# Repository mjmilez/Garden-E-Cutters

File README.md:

# Garden E-Cutters

## Overview
The Garden E-Cutters shears are a smart harvesting tool that records each cut event along with high-accuracy GPS data. When a cut is detected, the system captures an RTK-corrected GNSS position, logs the event locally, and transmits it to a base station for visualization on a live map dashboard.

## Key Features
- RTK GNSS positioning (u-blox ZED-F9P) for centimeter-level accuracy  
- Hall effect sensor-based cut detection  
- ESP32-based embedded control system  
- Local CSV logging for offline reliability  
- Bluetooth Low Energy (BLE) data transfer to base station  
- Audible and LED feedback for user interaction  
- Debounced trigger logic to prevent duplicate cut events  

## How It Works
1. A cut is detected using a Hall effect sensor on the shears.  
2. The ESP32 captures the next valid GNSS (GNGGA) message from the ZED-F9P.  
3. The event (timestamp + GPS + fix data) is stored locally in a CSV buffer.  
4. When connected, data is transmitted over BLE to the base station.  
5. The base system visualizes cut locations on a map dashboard.

## Hardware
- ESP32 microcontroller  
- u-blox ZED-F9P RTK GNSS receiver  
- Hall effect sensor (cut detection)  
- Piezo buzzer (status feedback)  
- Status LEDs  
- Battery-powered field enclosure  

## Design Focus
- Low-latency cut-to-log workflow  
- Reliable operation under intermittent connectivity  
- Minimal power and compute load on the field device  
- Robust data capture even during GNSS or BLE interruptions  

## Status
Prototype validated in field-like testing with reliable event detection, RTK-level positioning, and stable end-to-end data transfer to the base system.

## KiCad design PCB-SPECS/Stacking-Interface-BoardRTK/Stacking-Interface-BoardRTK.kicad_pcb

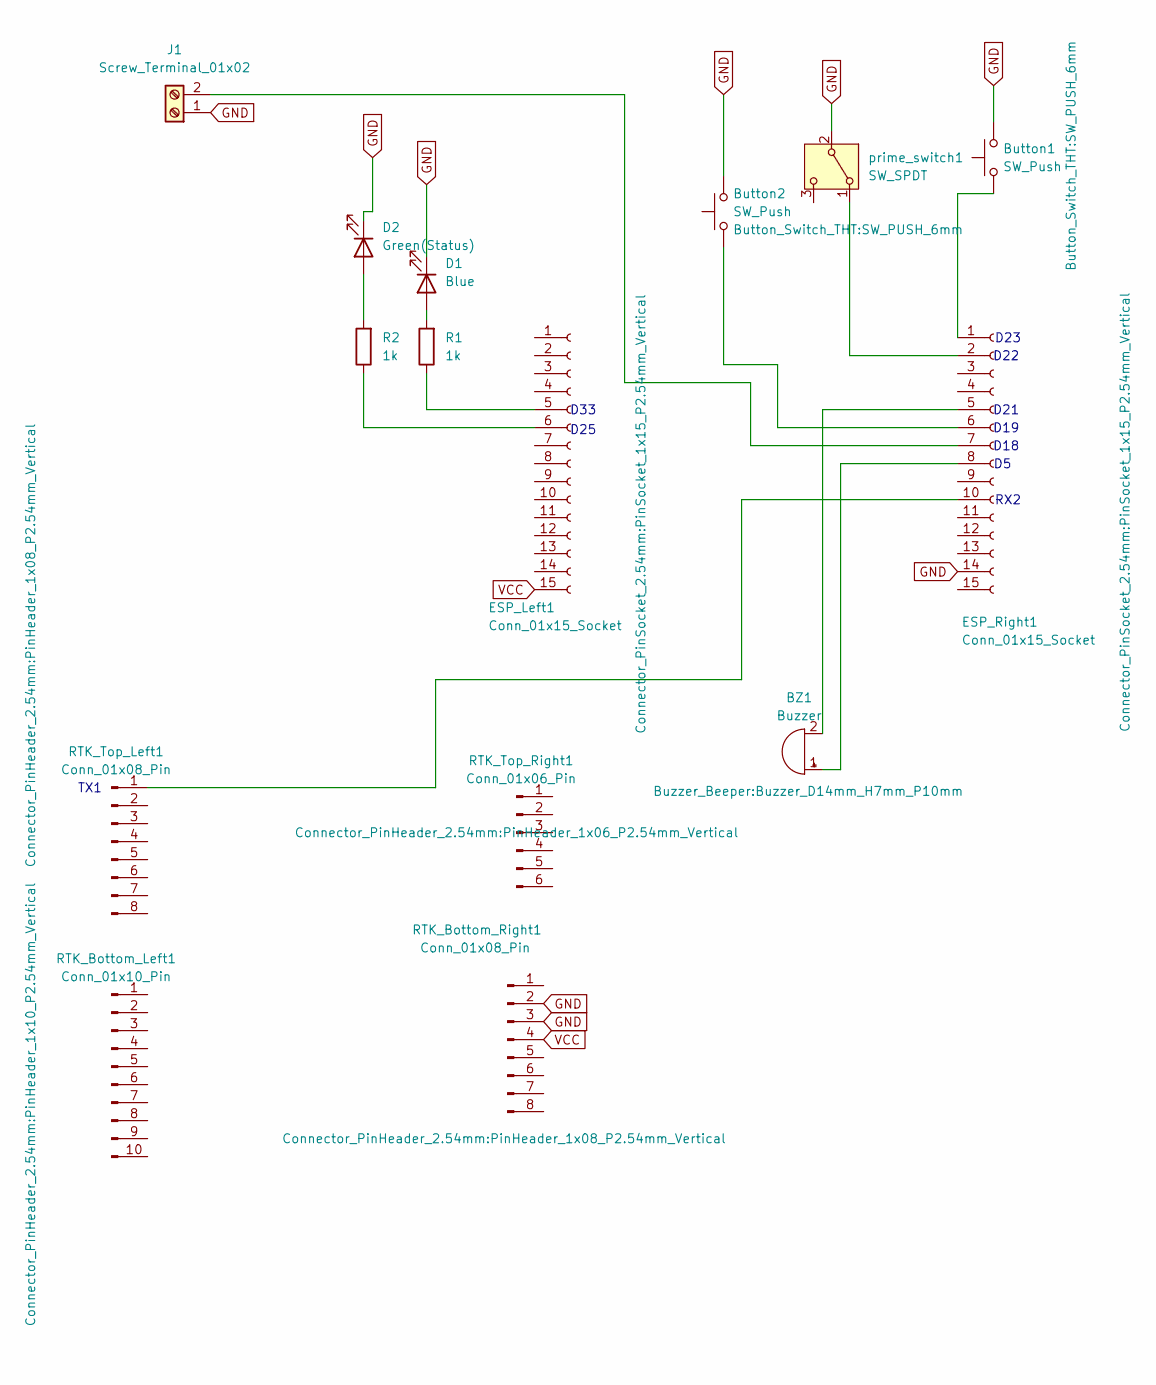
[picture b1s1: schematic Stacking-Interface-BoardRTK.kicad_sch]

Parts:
BZ1: Buzzer; Buzzer_D14mm_H7mm_P10mm
Button1, Button2: SW_Push; SW_PUSH_6mm
D1: Blue; LED_D1.8mm_W1.8mm_H2.4mm_Horizontal_O1.27mm_Z1.6mm
D2: Green(Status); LED_D1.8mm_W1.8mm_H2.4mm_Horizontal_O1.27mm_Z1.6mm
ESP_Left1: Conn_01x15_Socket; PinSocket_1x15_P2.54mm_Vertical
ESP_Right1: Conn_01x15_Socket; PinSocket_1x15_P2.54mm_Vertical
J1: Screw_Terminal_01x02; TerminalBlock_Altech_AK300-2_P5.00mm
R1, R2: 1k; R_Axial_DIN0207_L6.3mm_D2.5mm_P10.16mm_Horizontal
RTK_Bottom_Left1: Conn_01x10_Pin; PinHeader_1x10_P2.54mm_Vertical
RTK_Bottom_Right1: Conn_01x08_Pin; PinHeader_1x08_P2.54mm_Vertical
RTK_Top_Left1: Conn_01x08_Pin; PinHeader_1x08_P2.54mm_Vertical
RTK_Top_Right1: Conn_01x06_Pin; PinHeader_1x06_P2.54mm_Vertical
prime_switch1: SW_SPDT; spdt_switch

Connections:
GND: Button1.2, Button2.2, D1.1 (K), D2.1 (K), ESP_Right1.14, J1.1, RTK_Bottom_Right1.2, RTK_Bottom_Right1.3, prime_switch1.2 (B)
unnamed: BZ1.1 (+), ESP_Right1.8
unnamed: BZ1.2 (-), ESP_Right1.5
unnamed: D1.2 (A), R1.2
unnamed: D2.2 (A), R2.2
unnamed: ESP_Left1.5, R1.1
unnamed: ESP_Left1.6, R2.1
unnamed: Button1.1, ESP_Right1.1
unnamed: ESP_Right1.2, prime_switch1.1 (A)
unnamed: Button2.1, ESP_Right1.6
unnamed: ESP_Right1.7, J1.2
unnamed: ESP_Right1.10, RTK_Top_Left1.1 (TX1)
VCC: ESP_Left1.15, RTK_Bottom_Right1.4

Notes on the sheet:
D33
D21
D23
D22
RX2
D25
D19
TX1
D18

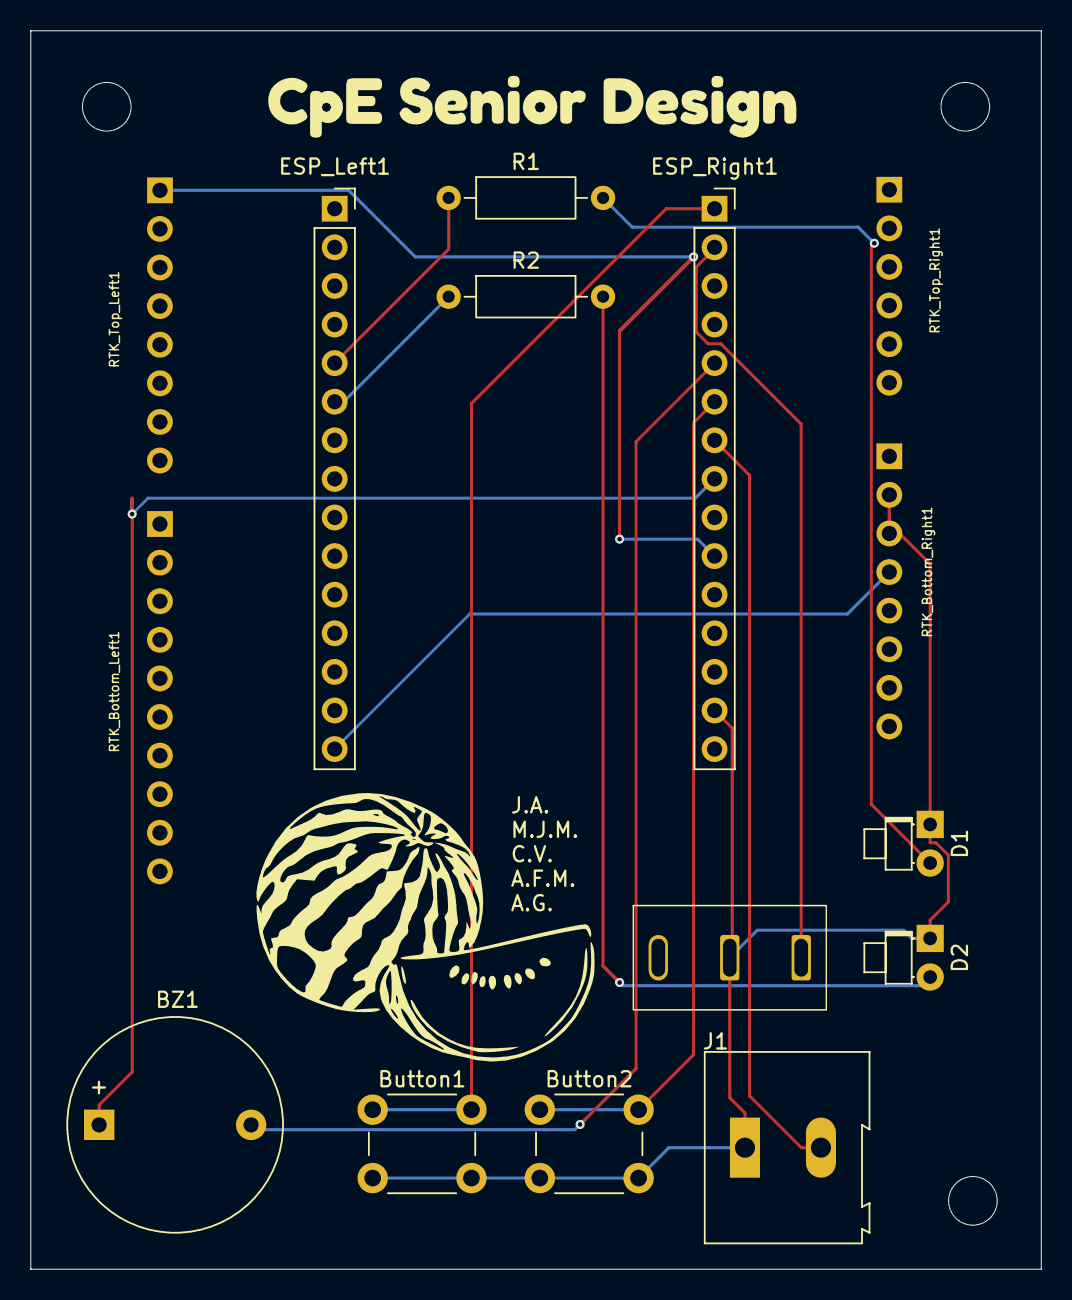
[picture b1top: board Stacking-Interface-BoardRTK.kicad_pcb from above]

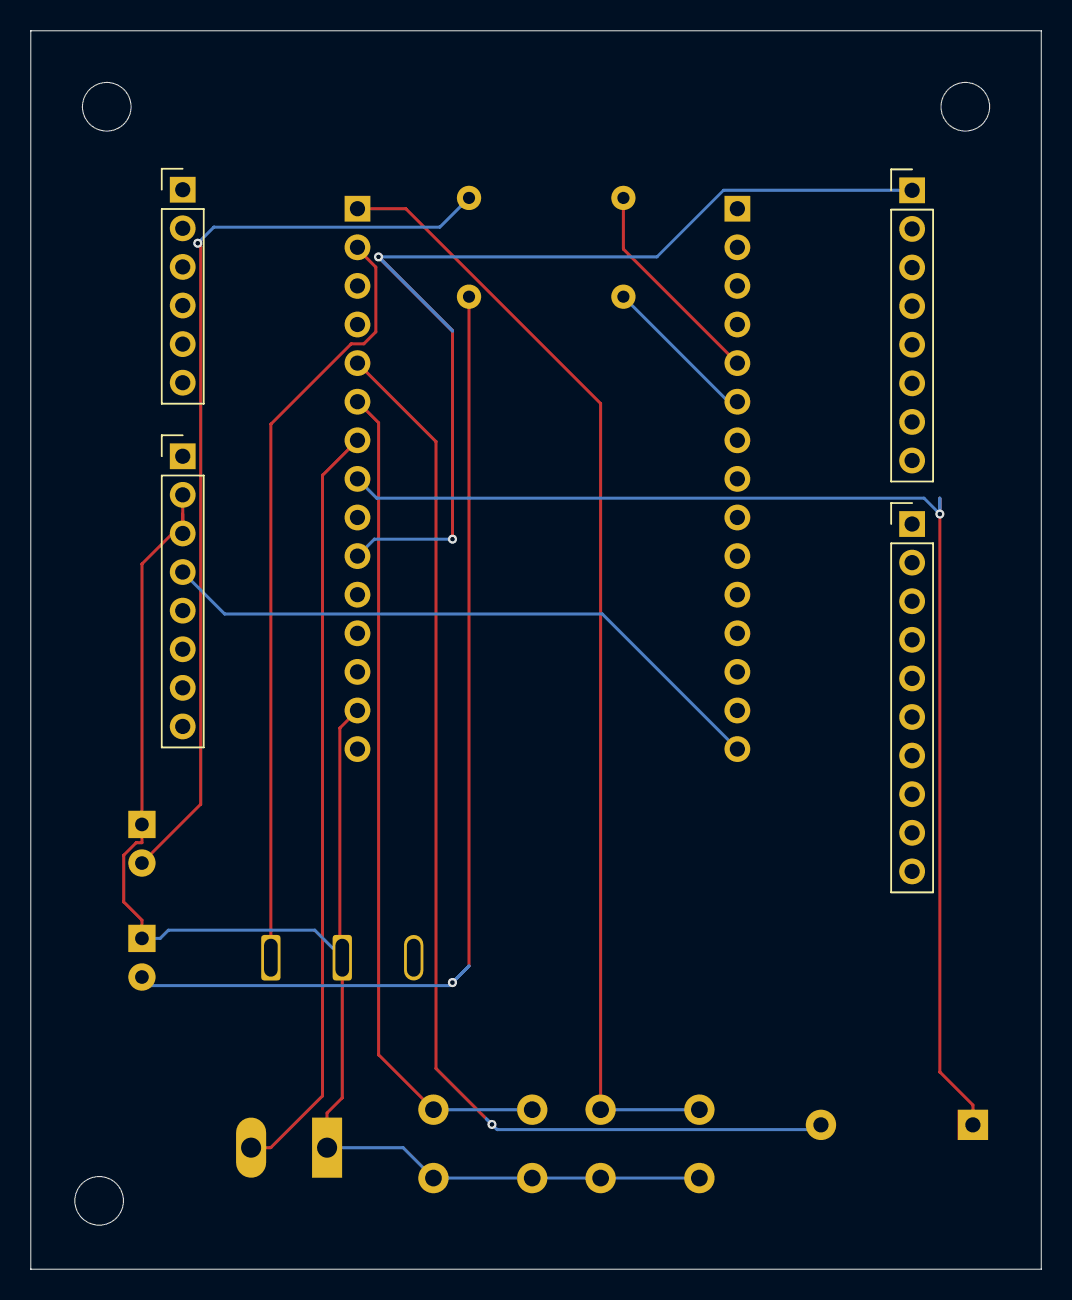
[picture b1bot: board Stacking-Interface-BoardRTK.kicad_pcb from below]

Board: 2 copper layers, 66.5 x 81.5 mm, 19 parts (4 on the bottom side), 13 nets.

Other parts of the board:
hole1, hole2, hole3: MountingHole_3.2mm_M3
kibuzzard-69A9F479: G***; kibuzzard-69A9F479

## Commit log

2025-10-27 Update README with project details and next steps
    Added detailed project overview, completed work, system architecture, known bugs, and next steps for the E-Cutter project.
2025-10-30 Added Fake Zed Directory
2025-10-30 test commit from VSCODE
2025-10-30 test commit
2025-10-30 practice1
2025-10-30 Another practice merge
2025-11-06 init: add project folders for shears-fw and base-fw
2025-11-06 Added .gitignore to maintain cleanliness in codebase
2025-11-12 Implemented a python simulator of NMEA code generator with tests. In a separate Arduino IDE I implemented a pseudo - I2C relationship component. Included the .c file that is uploaded. Still needs to 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
2025-11-13 Add clean ESP32 hub implementation without build artifacts
2025-11-13 initial web UI skeleton with dummy data and ID doc
2025-11-13 fixed column data
2025-11-14 Accomplished filtering/sorting functionality and pinning the coordinates on the map
2025-11-14 added red pin + preview data when hovering over them functionality
2025-11-14 fixed previewing bug from previous committ
2025-11-14 Working web server integration
2025-11-14 Integrate web UI with ESP32 hub - Add file serving handlers for HTML/CSS/JS/PNG - Connect frontend to /api/cuts endpoint - Add tooltip feature for map markers - Fix date format to MM/DD/YYYY - Auto-r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
2025-11-14 initial shears BLE advertising firmware using NimBLE (WM-SHEARS)
2025-11-14 bring up BLE peripheral and connection status LED
2025-11-14 implement BLE scan/connect logic with GPIO33 status LED
2025-11-14 Fixed merge mess up
2025-11-14 Updated shears BLE README.md
2025-11-14 Updated base station README.md
2025-11-14 Updated README.md w/ explanation and next steps
2025-11-16 updated document for dynamic front end element id's
2025-11-20 Broke down code into modules
2025-11-20 Broke down shears code into modules
2025-11-20 Integrated gps_logger into shears firmware.
2025-11-20 Updated shears README.md
2025-11-20 Updated base README.md
2025-11-20 Updated project README.md
2025-11-20 Add full BLE log transfer service (server side) to shears firmware
2025-12-01 Completed BLE file-transfer protocol (shears ↔ base) + full documentation overhaul
2025-12-02 Integrate Josh's BLE firmware with hub system
    - Added NimBLE support for BLE central functionality
    - Fixed all format specifier warnings (uint32_t -> %lu)
    - Adjusted partition table for larger binary (2MB app)
    - Integrated base_ble.c, log_transfer_client.c from Josh
    - Updated CMakeLists.txt with BLE source files
    - Created comprehensive README with setup/troubleshooting
2026-01-15 adding logs directory
2026-01-15 removing unnecessary directories
2026-01-15 log january 15th
2026-01-15 updating logs
2026-01-20 January 20th logs
2026-01-22 Oneview Note added
2026-01-22 Cleaned up codebase for main merge
2026-01-22 Updated header for clarity
2026-01-22 Updated all code with accurate documentation for clarity
2026-01-22 Prepped root README for merge
2026-01-22 Prepped README for main merge
2026-01-27 log for 01-27
2026-01-27 Fixed shears_led.c missing code issue
2026-01-27 Integrate Josh's BLE into watermelonHub
    - Added base_ble.c, base_led.c, log_transfer_client.c to main/
    - Added log_transfer component
    - Updated main.cpp with BLE initialization and connection callback
    - Updated CMakeLists.txt for NimBLE dependencies
    - Updated sdkconfig.defaults for NimBLE configuration
    - Updated partitions.csv (1200K factory, 1800K storage)
2026-01-27 clearing buffer code
2026-01-27 changes to the fake zed for bauderate testing
2026-01-27 Fixed shears_led.c missing code
2026-01-27 Modified print function to have line numbers and only print 5 most recent lines of gps_points.csv for debugging purposes.
2026-01-27 Updated baud rate and formatted the csv printing
2026-01-27 updating log
2026-01-27 Log for the day
2026-01-27 Chris Logs for 1/27
2026-01-29 Add Alessandro activity logs
2026-01-29 Add daily activity logs
2026-01-29 updating gitignore for mac and updating gps_logger.c
2026-01-29 adding clear csv functionality on 2 sec press down
2026-01-29 refined gps_logger by now waiting for next GGA sentence
2026-01-30 Add section for known bugs in README
2026-01-30 mock of how we want leaflet.js to render on our rasberry pi
2026-01-30 logs for chris over the past 2 days
2026-02-10 added 5 io peripherals!
2026-02-10 pwm for piezo
2026-02-10 double voltage for piezo, and fixing clear logic
2026-02-11 Added Raspberry Pi firmware runtime skeleton
2026-02-11 Added README.md for system service setup
2026-02-11 Added GPIO LED driver (base_led.c / .h)
2026-02-12 Started The Stacking Interface BoardRTK in kiCad project, for version control I will be saving and iterating it in github for others to open and see as well
2026-02-16 Updates to schematic, now all include digital footprints
2026-02-16 Okay Have a PCB design still need to measure the actual pins to make sure it's 100% accurate and figure out the fill and such
2026-02-16 Really trying to get the PCB okay... will have to work on it tmr
2026-02-17 Pi base port, ESP handles BLE and UART TX to Pi, Pi hosts and serves web server, public api for data access and retrieval
2026-02-18 Fixed gps_points.csv not being sent correctly due to chunk size mismatch
2026-02-18 UART from ESP32 defined and started. Need RPi to build and test reciever
2026-02-19 make spdt switch work!
2026-02-19 Updated Pi Base Code for UART RX, DB changes for updated packet
2026-02-23 Updated UART transfer pins
2026-02-25 Updated UART pins for base esp -> base rpi data transfer
2026-02-25 Ignoring pycache folder
2026-02-25 Ignore recieved files
2026-02-25 florida map leaflet.js changes
2026-02-25 deleted unneccessary markdown file
2026-02-25 deleted other files
2026-02-25 updated file structure for rpi
2026-02-25 Updated git ignore
2026-02-25 Merged from feature/web-ui. Needs cleanup still
2026-02-25 Updated app.js to pull from /api/cuts endpoint
2026-02-25 Updated table to have all available data
2026-02-25 Updated app.js to include all available data
2026-02-25 Updated app.js to process UTC to EST
2026-03-03 Working on PCB, got the correct measurements for correct stacking with microcontroller elements
2026-03-03 updating pcb
2026-03-03 pcb done
2026-03-04 Added shears_piezo.h and .c and removed piezo function definitions from gps_logger.c
2026-03-04 Added shears_primeSwitch.c and updated gps_logger.c to match
2026-03-04 Added shears_gpsButtons.c and removed redundant code from gps_logger.c
2026-03-04 Separated SPIFFS functions from gps_logger for shears firmware
2026-03-05 Add soft delete, restore, export, and auto-purge endpoints for dashboard
2026-03-05 fixing buggy trigger, now works
2026-03-05 changed millsecond debounce
2026-03-05 finished designing pcb
2026-03-05 updating logs bois
2026-03-06 adding production files
2026-03-10 adding step files
2026-03-10 feat: add POST /api/cuts debug endpoint for dev testing
2026-03-10 Added start_app.sh shell script
2026-03-10 Add manual cut create/delete and HDOP visualization modes
2026-03-10 Updated start_app.sh to safely pull from main
2026-03-10 Fixed capitalization issue
2026-03-10 Added base-app.service to run app.py as a service on reboot
2026-03-10 Updated base-app.service
2026-03-12 edited the db for cuts
2026-03-12 feat: enhance cut management with manual input and HDOP support
    - Added a new section in the UI for manually adding cuts, including fields for latitude, longitude, HDOP, and UTC time.
    - Implemented functionality to handle HDOP values in the backend, allowing for more precise cut data.
    - Introduced a delete feature for selected cuts in the UI.
    - Updated styles for the new input panel and buttons.
    - Enhanced map rendering to reflect HDOP values in marker sizes and opacities.
2026-03-12 Stop tracking local database file
2026-03-12 Updated base esp -> base rpi transfer to happen automatically rather than from a button press
2026-03-12 date ield added in UI
2026-03-12 Updated .gitignore
2026-03-12 Remove deprecated base-data-fw and base-ble-fw directories
2026-03-12 Updated to automatically clear the CSV file after a transfer is completed
2026-03-12 Add log entry for Christian Veltchev's lab day on 3/12/2026, detailing RC check-in and functionality tests
2026-03-12 Add UTC Date field to shears csv and pi database.
2026-03-12 Added quadruple beep when assert to csv fails
2026-03-12 Fix insert_cut missing utc_date param.
2026-03-12 Fix debug print table for 9-column CSV with utc_date
2026-03-12 Updated files to automatically transfer csv file if connected to bluetooth during a cut
2026-03-12 Adjust header detection in uart rx.py file.
2026-03-12 Updated app.js to poll for new cuts for live updates
2026-03-12 Update app.js to show date in table
2026-03-24 Fix status indicator, date filter, and manual cut date persistence
2026-03-24 Replace app.js with fixed version (status indicator, date filter, date persistence)
2026-03-24 Display dates as MM/DD/YYYY
2026-03-24 Fix Date not displaying on UI bug.
2026-03-24 Add auto network mode switching (hotspot vs AP) to boot scripts
2026-03-24 Small change to boot scripts sleeps while hotspot connection is configured
2026-03-25 log 03-24-2026
2026-03-25 Add deleted cuts management feature with retention and recovery options
    - Introduced a new tab for managing deleted cuts, including a retention policy of 48 hours.
    - Implemented functions to fetch, display, and recover deleted cuts.
    - Enhanced UI with buttons for exporting CSV and recovering selected deleted cuts.
    - Updated styles for the new deleted cuts table and controls.
2026-03-25 Add lab day log for March 24, 2026, detailing UI enhancements and team meetings
    - Documented accomplishments including CSV export functionality and deleted cuts management.
    - Noted updates to frontend API routing and team discussions on project progress and design alterations.
    - Total working time recorded as 5 hours.
2026-03-26 Adjust service files so Pi searches for hotspot after networkManager service completes
2026-03-26 Adjust max zoom for leaflet map
2026-03-26 Fix startup bash scripts
2026-03-30 Add log entry for March 30, 2026
2026-03-30 pcb with components
2026-03-30 adding SolidWorks files
2026-03-31 Switch map accuracy to fix type and add manual fix quality input
2026-03-31 Leaflet.js offline features implemented
2026-03-31 merge: resolve conflicts, add offline tiles + fix_quality support
2026-03-31 offline leaflet functionality implemented
2026-03-31 bug fix: website broke lol
2026-04-02 Ensure offline map loads at a cached location
2026-04-02 Add fix quality display andupdates in logs and deleted cuts sections
2026-04-02 Add log entry for Christian Veltchev's lab day on 4/2/2026, detailing UI modernization efforts and total working time.
2026-04-03 editing gpio pin for PCB
2026-04-03 Add log entry for Christian Veltchev's demo day on 4/3/2026, highlighting accomplishments and areas for improvement.
2026-04-07 Added 7 segment functionality (pinouts still need to be updated)
2026-04-08 Add log for project presentation preparation
2026-04-14 clean repo
2026-04-17 Add README for Garden E-Cutters project
    Added comprehensive documentation for the Garden E-Cutters shears, detailing features, operation, hardware, design focus, and status.
2026-04-17 Simplify README title by removing subtitle
    Removed the subtitle from the README for clarity.
